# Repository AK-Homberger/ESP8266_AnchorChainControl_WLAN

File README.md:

# Anchor Chain Control with WLAN

This is a port from the ESP32 repository to a ESP8266 D1 Mini which is smaller than the ESP32 Node MCU.

## Caution: This is the updated version 1.2 with changed I/O pin definitions! The PCB is also updated but untested.

This repository shows how to remotely control the anchor chain relay via WLAN from phone/tablet.
Anchor chain events from the chain sensor are measured and presented on the phone/tablet.

Just set the WLAN ssid and password according to your needs. 
Select WLAN type with setting WiFiMode_AP_STA to "0" means Acess Point, or "1" means Client with DHCP.

Also set Chain_Calibration_Value according to your sensor (e.g. 0.33. meter per event).

If working as Access Point, connect the phone/tablet to the defined AP and start "192.168.4.1" in the browser.
If working as WLAN client, check the DHCP IP address with Serial Monitor of IDE and start browser with the shown IP address.

To control the anchor chain relay just press:
- "Down" for anchor down
- "Up" for anchor up
- "Stop" for Stop
- "Reset" to reset the chain counter to zero

Features:
- Saftey stop to stop "anchor up" two events before reaching zero (can be changed in code with SAFETY_STOP).
- Safety stop if maximum chain lenght is reached (standard 40 meters, can be changed with MAX_CHAIN_LENGTH)
- Watchdog timer to stop power after 1 second inactivity of client (e.g. due to connection problems).
- Watchdog timer to detect blocking chain. Engine stops if no events are detected within 1 second for up/down command.
- Current Chain Counter is stored in nonvolatile memory. ESP can be switched off after anchoring (counter is restored after new start).
- Demo mode to check functionality without having a windlass / chain counter connected to ESP (set ENABLE_DEMO to 1).

A [pcb layout](https://github.com/AK-Homberger/ESP8266_AnchorChainContol_WLAN/blob/main/D1MiniChainCounterWLAN-Board.pdf) is available in the [KiCAD](https://github.com/AK-Homberger/ESP8266_AnchorChainControl_WLAN/tree/main/D1MiniChainCounterWLAN) folder: "D1MiniChainCounterWLAN.kicad_pcb".

You can order a PCB from Aisler.net: https://aisler.net/p/WJSHXVDM

The current design should work for a Quick or Lofrans anchor chain relay and chain sensor (which looks like a simple reed relay triggerd from a magnet). Connection details  for a Quick windlass/counter can be found here: https://www.quickitaly.com/resources/downloads_qne-prod/1/CHC1203_IT-EN-FR_REV001A.pdf

Used I/O pins:

- D1/D2: Output, relais Up/Down
- D6/D7: Input, manual override detection Up/Down (option)
- D5: Input, chain sensor 

With these IO pins the boot problem with the relais should be solved. Details see here: https://randomnerdtutorials.com/esp8266-pinout-reference-gpios/
The former version used D4/D5 as relais output istead of safe GPIO4(D1) and GPIO5(D2). D5,D6,D7 are safe for input.

The manual override detection function with D6/D7 is currently missing in the code. Feel free to support/update.

If you have problems with the chanin counter input measuring multiple count signals, it might be necessary to use a library to avoid multiple counts e.g.: https://github.com/mathertel/OneButton

You can easily do your own changes now: I added the full KiCAD details: https://github.com/AK-Homberger/ESP8266_AnchorChainControl_WLAN/tree/main/D1MiniChainCounterWLAN

## Parts:

- Board [Link](https://aisler.net/p/WJSHXVDM)
- U1 D1 Mini [Link](https://www.reichelt.de/de/en/d1-mini-esp8266-v3-0-d1-mini-p253978.html?&nbc=1)
- J2 D24V10F5 [Link](https://eckstein-shop.de/Pololu-5V-1A-Step-Down-Spannungsregler-D24V10F5)
- R1 Resistor 1 KOhm [Link](https://www.reichelt.de/de/en/carbon-film-resistor-1-4-w-5-1-0-kilo-ohms-1-4w-1-0k-p1315.html?&trstct=pos_2&nbc=1)
- R2, R3 Resistor 270 Ohm (*2) [Link](https://www.reichelt.de/de/en/carbon-film-resistor-1-4-w-5-270-ohm-1-4w-270-p1390.html?&nbc=1)
- R4, R5 Resistor 10 KOhm (*2) [Link](https://www.reichelt.de/de/en/carbon-film-resistor-1-4w-5-10-kilo-ohms-1-4w-10k-p1338.html?&nbc=1)
- Q1, Q2, Q3, Q4 Transistor BC337 (*4) [Link](https://www.reichelt.de/de/en/transistor-to-92-bl-npn-45v-800ma-bc-337-25-dio-p219125.html?&nbc=1)
- D2, D3 Diode 1N4148 (*2) [Link](https://www.reichelt.de/schalt-diode-100-v-150-ma-do-35-1n-4148-p1730.html?search=1n4148)
- D1 Diode 1N4001 [Link](https://www.reichelt.de/de/en/rectifier-diode-do41-50-v-1-a-1n-4001-p1723.html?&nbc=1)
- U2 H11-L1 [Link](https://www.reichelt.de/optokoppler-1-mbit-s-dil-6-h11l1m-p219351.html?search=H11-l1)
- K1, K2 Relay (*2) [Link](https://www.reichelt.de/de/en/miniature-power-relay-g5q-1-no-5-v-dc-5-a-g5q-1a-eu-5dc-p258331.html?&nbc=1)
- J1, J3, J4 Connector 2-pin (*3) [Link](https://www.reichelt.de/de/en/2-pin-terminal-strip-spacing-5-08-akl-101-02-p36605.html?&nbc=1)

## Updates:

- 06.10.2021 - Version 1.2: Changed IO pins to avoid problem during boot and preparation for correct manual override detection.
- 06.11.2020 - Changed PCB layout to version 1.1. Larger terminal blocks (5.08 mm) and different transistor footprints for easy soldering.
- 02.11.2020 - Version 1.0: Initial version with ESP8266 D1 Mini.

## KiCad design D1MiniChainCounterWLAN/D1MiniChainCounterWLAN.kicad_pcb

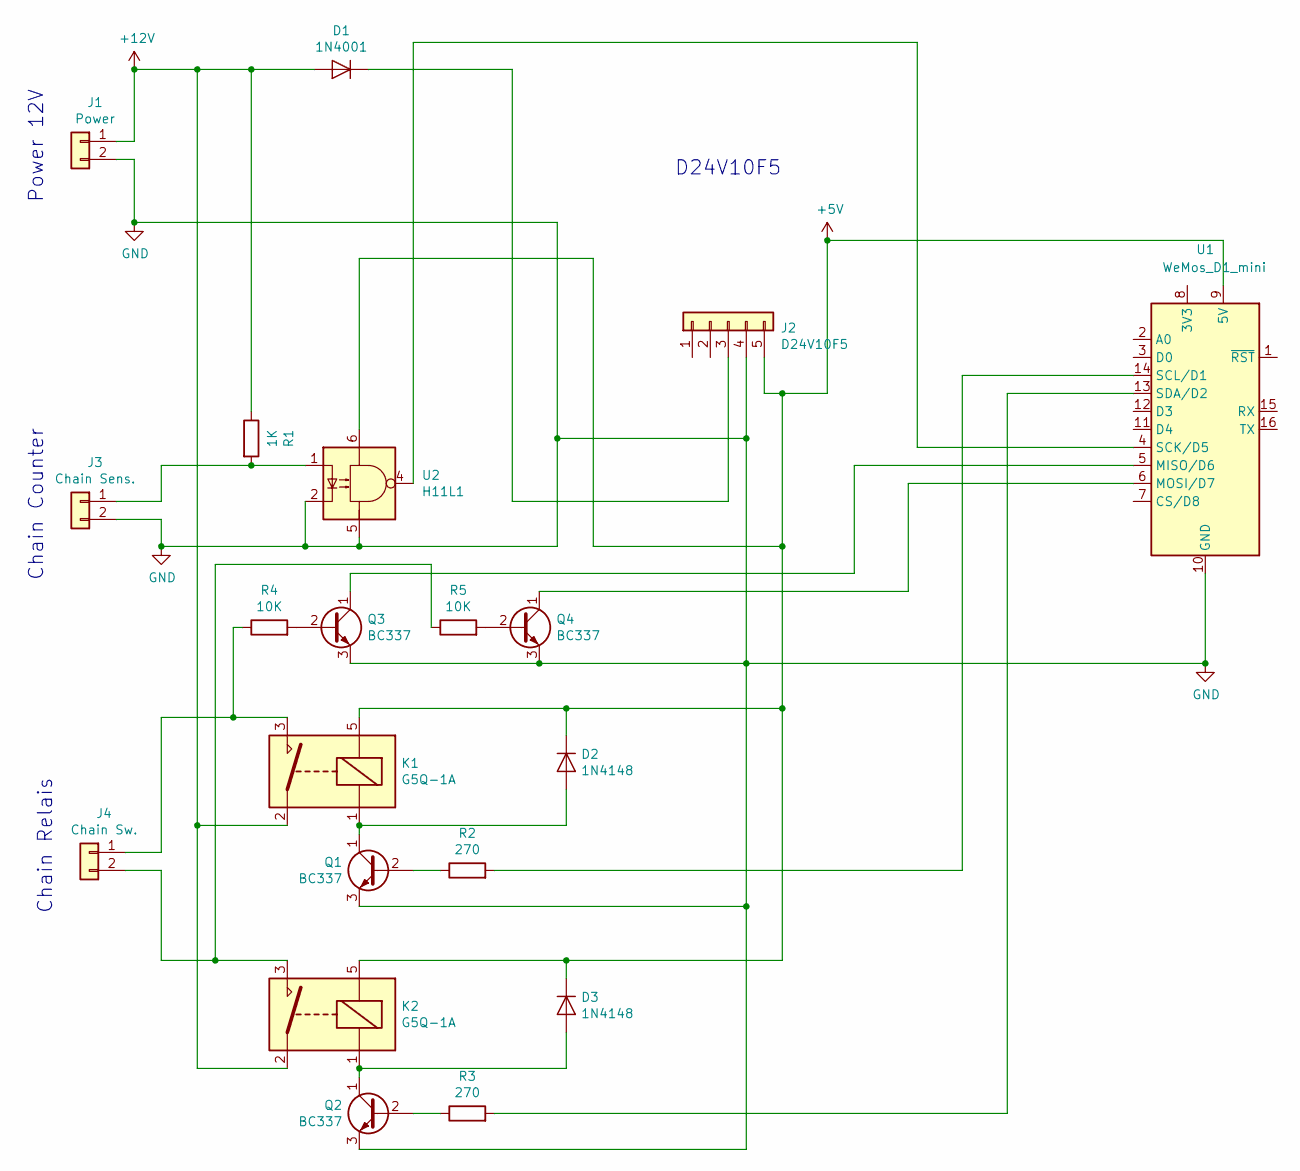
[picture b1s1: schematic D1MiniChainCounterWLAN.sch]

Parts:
D1: 1N4001; D_DO-41_SOD81_P10.16mm_Horizontal
D2, D3: 1N4148; D_DO-35_SOD27_P7.62mm_Horizontal
J1: Power; TerminalBlock_bornier-2_P5.08mm
J2: D24V10F5; PinHeader_1x05_P2.54mm_Vertical
J3: Chain Sens.; TerminalBlock_bornier-2_P5.08mm
J4: Chain Sw.; TerminalBlock_bornier-2_P5.08mm
K1, K2: G5Q-1A; Relay_SPST_Omron-G5Q-1A
Q1, Q2, Q3, Q4: BC337; TO-92_HandSolder
R1: 1K; R_Axial_DIN0207_L6.3mm_D2.5mm_P7.62mm_Horizontal
R2, R3: 270; R_Axial_DIN0207_L6.3mm_D2.5mm_P7.62mm_Horizontal
R4, R5: 10K; R_Axial_DIN0207_L6.3mm_D2.5mm_P7.62mm_Horizontal
U1: WeMos_D1_mini; WEMOS_D1_mini_light
U2: H11L1; DIP-6_W7.62mm

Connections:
+5V: D2.1 (K), D3.1 (K), J2.5, K1.5, K2.5, U1.9 (5V), U2.6
+12V: D1.2 (A), J1.1, K1.2, K2.2, R1.1
GND: J1.2, J2.4, J3.2, Q1.3 (E), Q2.3 (E), Q3.3 (E), Q4.3 (E), U1.10 (GND), U2.2, U2.5
unnamed: D1.1 (K), J2.3
unnamed: D2.2 (A), K1.1, Q1.1 (C)
unnamed: D3.2 (A), K2.1, Q2.1 (C)
unnamed: J3.1, R1.2, U2.1
unnamed: J4.1, K1.3, R4.1
unnamed: J4.2, K2.3, R5.1
unnamed: Q1.2 (B), R2.1
unnamed: Q2.2 (B), R3.1
unnamed: Q3.1 (C), U1.5 (MISO/D6)
unnamed: Q3.2 (B), R4.2
unnamed: Q4.1 (C), U1.6 (MOSI/D7)
unnamed: Q4.2 (B), R5.2
unnamed: R2.2, U1.14 (SCL/D1)
unnamed: R3.2, U1.13 (SDA/D2)
unnamed: U1.4 (SCK/D5), U2.4

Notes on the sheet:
D24V10F5
Chain Counter
Power 12V
Chain Relais

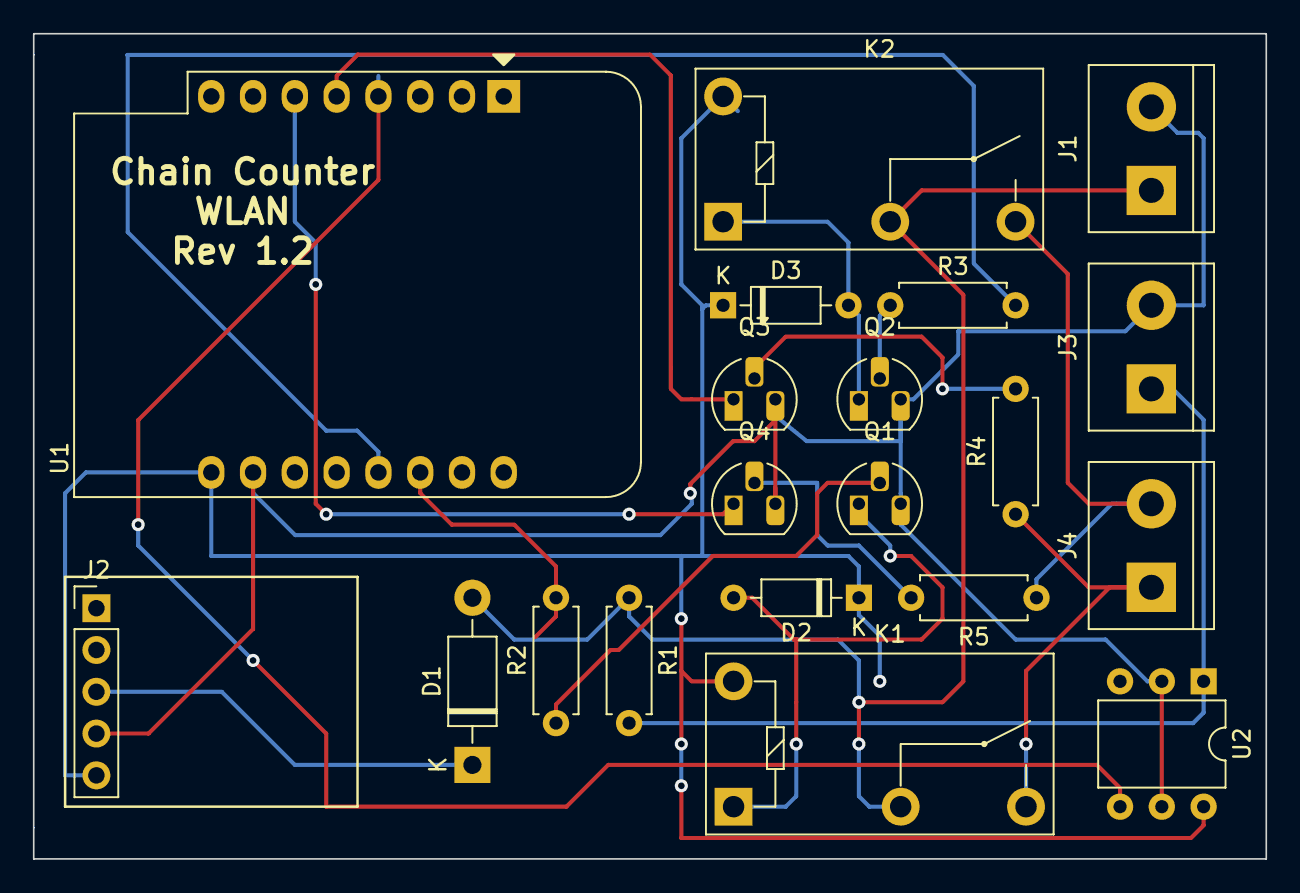
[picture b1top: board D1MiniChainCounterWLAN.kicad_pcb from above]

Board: 2 copper layers, 74.9 x 50.2 mm, 20 parts (0 on the bottom side), 18 nets.

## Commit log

2020-11-06 Version 1.1
2021-10-06 KiCAD Version 1.2 files
2021-10-06 Version 1.2 (Changed IO pins)
2021-10-06 Version 1.2 (Changed IO pims)
2021-10-06 Version 1.2 (updated IO pins)
